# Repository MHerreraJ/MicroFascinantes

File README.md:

<meta name="google-site-verification" content="56YGGNdEkGo94rvDZRkzSX_00WQJ7aJo11EX2UVtsUU" />
# MicroFascinantes

Proyecto de la Secretaria de Educación, Ciencia, Tecnología e Innovación (SECTEI) del Gobierno de la CDMX y el Instituto de Ingeniería de la UNAM para acercar a jóvenes y niños a las microtecnologías.

# Contenido
El repositorio en cuestión contiene todos los documentos referentes al taller de Tatuajes Inteligentes, donde se incluyen los siguientes archivos:
* **Taller "Tatuajes Inteligentes"**
   * *Actividad "Dibuja tu primer circuito eléctrico"*
     * **[README.md]** Descripción de la actividad.
     * **[Material.pdf]** Documento que especifica los materiales a utilizar y donde se pueden conseguir. 
     * **[Diseños.pdf]** Documento con los diseños utilizados en el Taller.
     * **[Instrucciones.pdf]** Instrucciones.
   * *Actividad "Programa tu tatuaje inteligente"*
     * **[README.md]** Descripción de la actividad.
     * **[Material.pdf]** Documento que especifica los materiales a utilizar y donde se pueden conseguir. 
     * **[Diseño.pdf]** Diseño utilizado.
     * **[Arduino]** Código fuente utilizado para controlar el programador NFC.
     * **[Python]** Código fuente con la interfaz usada para rellenar el formulario de datos del tatuaje.   
     * **[Instrucciones.pdf]** Instrucciones.
   * *Actividad "Control remoto con un tatuaje"*
     * **[README.md]** Descripción de la actividad.
     * **[Material.pdf]** Documento que especifica los materiales a utilizar y donde se pueden conseguir. 
     * **[Diseño.pdf]** Diseño utilizado.
     * **[Tatuaje]** Archivos de la parte del tatuaje.
       * **[EAGLE]** Esquemático del circuito impreso de la pulsera (EAGLE).
       * **[MPLAB]** Código fuente en C del control remoto pulsera.
       * **[Diseño.pdf]** Diseño del tatuaje utilizado.
     * **[Foco]** Archivos de la parte de control de brillo.
       * **[EAGLE]** Esquemático del circuito impreso del Shield de Control de Potencia para Arduino (EAGLE).
       * **[Arduino]** Código fuente del Arduino para recibir información de la pulsera y controlar el Shield.
     * **[Instrucciones.pdf]** Instrucciones.

# Páginas Web
>[Instituto de Ingeniería] http://www.iingen.unam.mx<br/>
>[Facebook Microfascinantes] https://www.facebook.com/Microfascinantes/<br/>
>[Secretaria de Educación, Ciencia, Tecnología e Innovación] https://www.sectei.cdmx.gob.mx/<br/>

# Contacto
>[Tatuajes Inteligentes] Dr. Roberto Ramirez: roberto.ramirez@icat.unam.mx <br/>
>[Tatuajes Inteligentes] Manuel Herrera: herrera.juarez.manuel@outlook.com <br/>
<br/><br/><br/>
<p float="center">
  <div class="frame" style="height: 25px;">
      
  </div>
  <div class="frame" style="height: 25px;">
      
  </div>
</p>

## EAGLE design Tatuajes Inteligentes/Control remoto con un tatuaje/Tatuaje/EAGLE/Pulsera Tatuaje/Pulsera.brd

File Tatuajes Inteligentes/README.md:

# Tatuajes Inteligentes
Este taller tiene el propósito de enseñar los conceptos sobre qué es un circuito eléctrico, y como podemos construir uno.
El taller cuenta con tres actividades:
* Dibuja tu circuito eléctrico.
* Programa tu tatuaje inteligente.
* Controla algo desde tu piel.

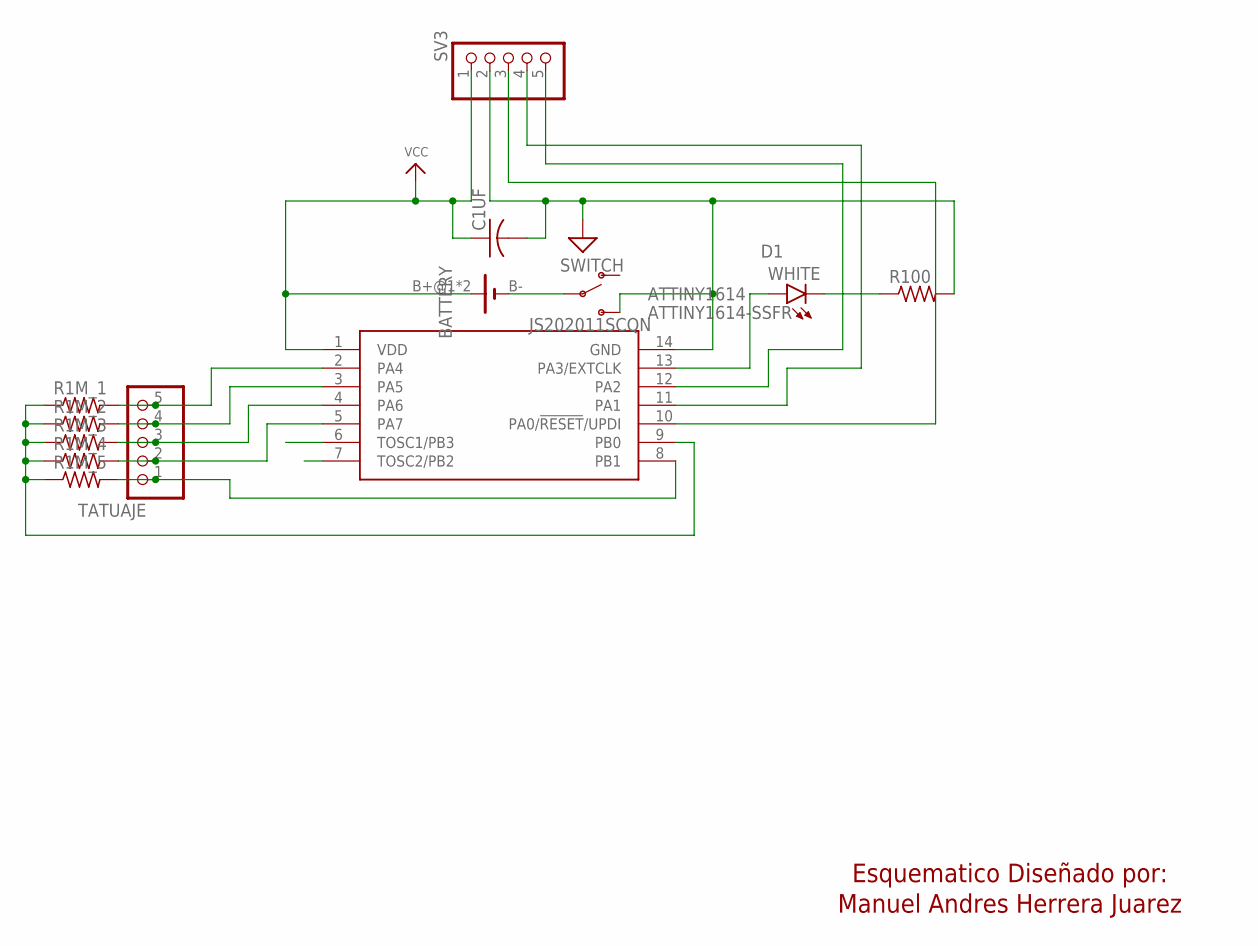
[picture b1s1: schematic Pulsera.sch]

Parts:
ATTINY1614: ATTINY1614-SSFR; SOIC127P600X175-14N
BATTERY: BAT_HLD_CR12; CR12-HOLDER
C1UF: C-USC1206; C1206
D1: WHITE; LED-1206
R1M_1, R1M_2, R1M_3, R1M_4, R1M_5, R100: R-US_R1206; R1206
SV3: PINHD-1X5; 1X05
SWITCH: JS202011SCQN
TATUAJE: PINHD-1X5; 1X05

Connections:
GND: ATTINY1614.14 (GND), C1UF.2, R100.2, SV3.2, SWITCH.B2 (2), SWITCH.L2 (2)
unnamed: D1.C, R100.1
unnamed: ATTINY1614.10 (PA0/!RESET!/UPDI), SV3.3
unnamed: ATTINY1614.9 (PB0), R1M_1.1, R1M_2.1, R1M_3.1, R1M_4.1, R1M_5.1
unnamed: ATTINY1614.11 (PA1), SV3.4
unnamed: ATTINY1614.5 (PA7), R1M_4.2, TATUAJE.2
unnamed: ATTINY1614.8 (PB1), R1M_5.2, TATUAJE.1
unnamed: ATTINY1614.4 (PA6), R1M_3.2, TATUAJE.3
unnamed: ATTINY1614.3 (PA5), R1M_2.2, TATUAJE.4
unnamed: ATTINY1614.2 (PA4), R1M_1.2, TATUAJE.5
unnamed: ATTINY1614.12 (PA2), SV3.5
unnamed: ATTINY1614.13 (PA3/EXTCLK), D1.A
unnamed: BATTERY.B- (-), SWITCH.BC (C), SWITCH.LC (C)
VCC: ATTINY1614.1 (VDD), BATTERY.B+@1 (+), BATTERY.B+@2 (+), C1UF.1, SV3.1

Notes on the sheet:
Esquematico Diseñado por: Manuel Andres Herrera Juarez

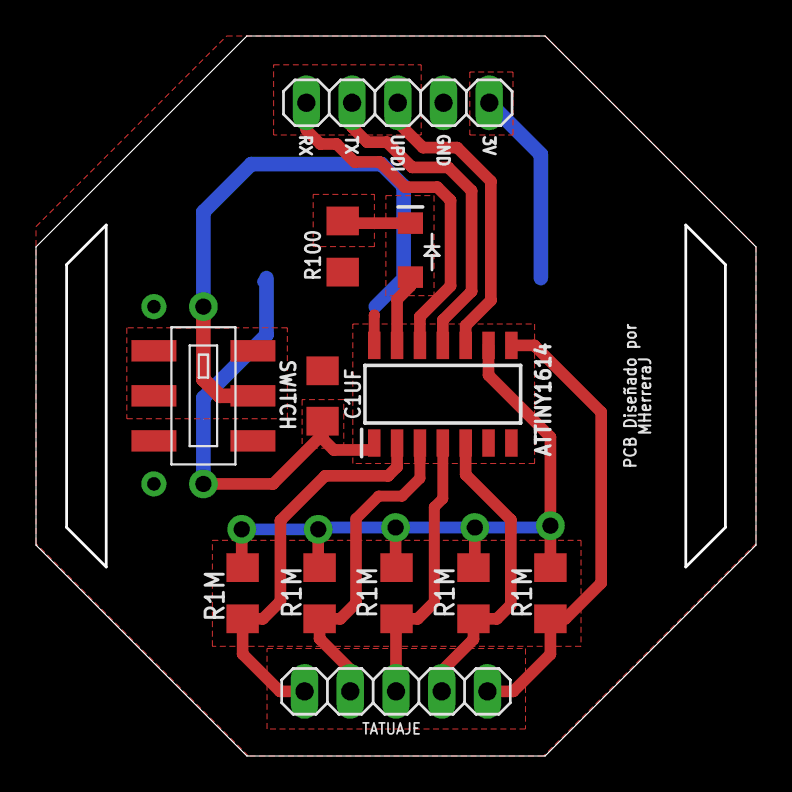
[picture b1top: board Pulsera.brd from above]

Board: 2 copper layers, 39.8 x 39.8 mm, 13 parts (1 on the bottom side), 14 nets.

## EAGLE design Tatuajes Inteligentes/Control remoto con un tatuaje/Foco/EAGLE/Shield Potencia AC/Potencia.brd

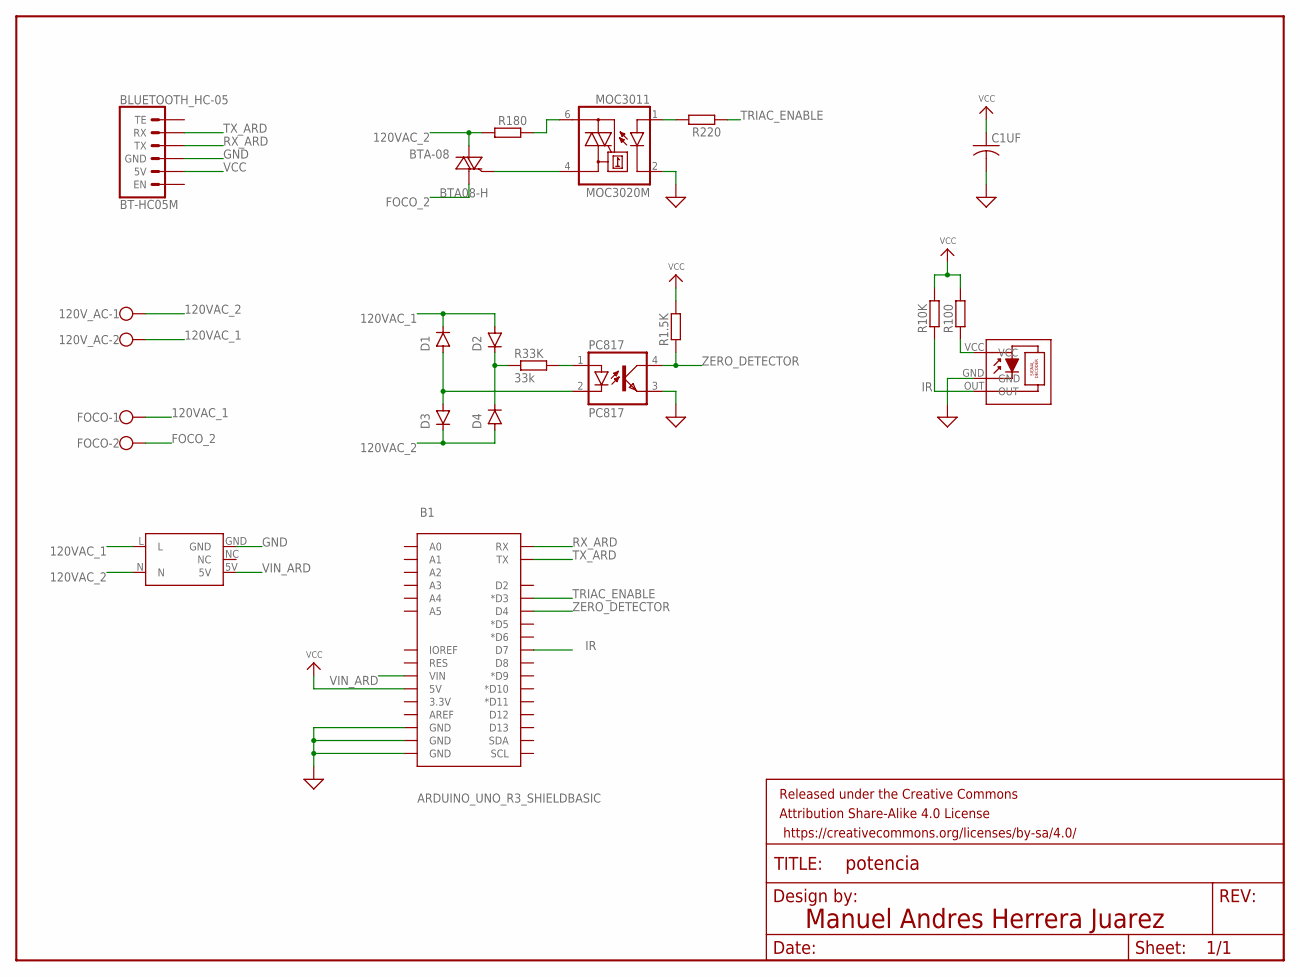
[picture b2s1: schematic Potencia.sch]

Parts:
120V_AC: W237-102
B1: ARDUINO_UNO_R3_SHIELDBASIC; UNO_R3_SHIELD
BLUETOOTH_HC-05: BT-HC05M; HEADER1X6
BTA-08: BTA08-H; TO220BH
C1UF: C-USC1206; C1206
D1, D2, D3, D4: 1N4007; DO-41
FOCO: W237-102
FRAME2: FRAME-LETTERNO_PACKAGE; DUMMY
IR1838: VS138; TO92-BCE
MOC3011: MOC3020M; DIL06
PC817: PC817; DIL04
R1.5K, R10K, R100, R220: R-EU_0207/10; 0207/10
R33K: 33k; 0411/15
R180: R-EU_0204/7; 0204/7
U$1: 127VAC_5VDC_CONVERTER; 127AC_5DC_CONVERTER

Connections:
120VAC_1: 120V_AC.2, D1.C, D2.A, FOCO.1, U$1.L
120VAC_2: 120V_AC.1, BTA-08.T2 (A2), D3.C, D4.A, R180.2, U$1.N
FOCO_2: BTA-08.T1 (A1), FOCO.2
GND: B1.GND@0 (GND), B1.GND@1 (GND), B1.GND@2 (GND), BLUETOOTH_HC-05.P$4 (GND), C1UF.2, IR1838.GND, MOC3011.2 (C), PC817.3 (EMIT), U$1.GND
IR: B1.D7, IR1838.OUT, R10K.1
unnamed: D1.A, D3.A, PC817.2 (C)
unnamed: D2.C, D4.C, R33K.1
unnamed: IR1838.VCC, R100.1
unnamed: PC817.1 (A), R33K.2
unnamed: BTA-08.G, MOC3011.4 (A1)
unnamed: MOC3011.6 (A2), R180.1
unnamed: MOC3011.1 (A), R220.2
RX_ARD: B1.RX, BLUETOOTH_HC-05.P$3 (TX)
TRIAC_ENABLE: B1.D3 (*D3), R220.1
TX_ARD: B1.TX, BLUETOOTH_HC-05.P$2 (RX)
VCC: B1.5V, BLUETOOTH_HC-05.P$5 (5V), C1UF.1, R1.5K.2, R10K.2, R100.2
VIN_ARD: B1.VIN, U$1.5V
ZERO_DETECTOR: B1.D4, PC817.4 (COL), R1.5K.1

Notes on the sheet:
Manuel Andres Herrera Juarez

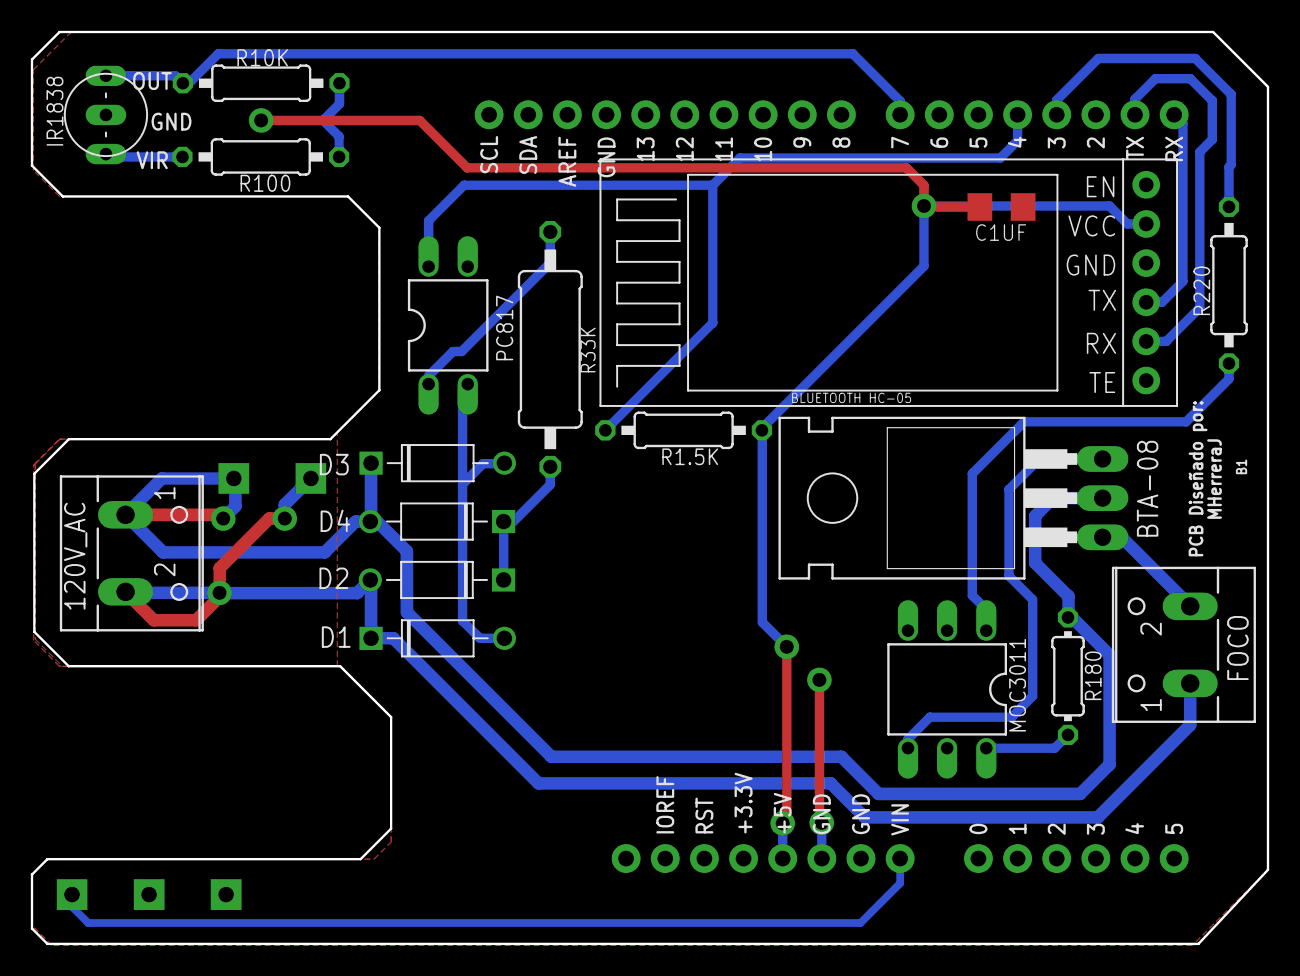
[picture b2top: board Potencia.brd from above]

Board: 2 copper layers, 80.2 x 59.2 mm, 21 parts (0 on the bottom side), 18 nets.

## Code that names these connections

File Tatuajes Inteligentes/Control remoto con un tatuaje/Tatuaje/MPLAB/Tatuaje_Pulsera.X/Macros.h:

/************************************************************
 * Macros.h                         Created on: 11/08/2019  *
 *                                                          *
 *      Universidad Nacional Autonoma de Mexico             *
 *              Instituto de Ingeniería                     *
 *          Gobierno de la Ciudad de México                 *
 *                  Microfascinantes                        *
 *                                                          *
 *  Desarrollador: Manuel Andres Herrera Juarez.            *
 *                                                          *
 ************************************************************/

#ifndef MACROS_H
#define	MACROS_H

#ifdef	__cplusplus
extern "C" {
#endif

#define ALLINONE_FIRMWARE   1
#define CONTROL_FIRMWARE    2
    
#define TYPEOF_FIRMWARE CONTROL_FIRMWARE
//#define TYPEOF_FIRMWARE  ALLINONE_FIRMWARE
    
#define F_CPU 5000000UL
#define  __DELAY_BACKWARD_COMPATIBLE__

#include <xc.h>
#include <avr/io.h>
#include <util/delay.h>
#include <avr/interrupt.h>
#include <stdlib.h>
#include <stdio.h>
#include <stdint.h>
#include <string.h>
#include <stdlib.h>
#include <stdarg.h>
#include <math.h>

#define IO_PA0     0x00
#define IO_PA1     0x01
#define IO_PA2     0x02
#define IO_PA3     0x03
#define IO_PA4     0x04
#define IO_PA5     0x05
#define IO_PA6     0x06
#define IO_PA7     0x07
    
#define IO_PB0     0x20
#define IO_PB1     0x21
#define IO_PB2     0x22
#define IO_PB3     0x23
#define IO_PB4     0x24
#define IO_PB5     0x25
#define IO_PB6     0x26
#define IO_PB7     0x27
    
    
#define GETIO_PORT(pin) ((((pin)>>4) == 0x00)? &PORTA : &PORTB)
#define GETIO_MASK(pin) ((uint8_t)(1<<((pin) & 0x07)))
#define GETIO_PIN(pin)  ((uint8_t)((pin) & 0x07))
    
#ifdef	__cplusplus
}
#endif

#endif	/* UTILS_H */

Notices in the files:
parts and their libraries:
SparkFun-Boards: Licensing: Creative Commons ShareAlike 4.0 International - https://creativecommons.org/licenses/by-sa/4.0
SparkFun-Aesthetics: Released under the Creative Commons Attribution Share-Alike 4.0 License
SparkFun-Aesthetics: https://creativecommons.org/licenses/by-sa/4.0
